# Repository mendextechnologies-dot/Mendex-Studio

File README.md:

# Mendex Engineering Studio v0.1.0 — foundation

**Product documents:** start at `C:\Mendex studio\Product Documents` or the
**Mendex Products** desktop shortcut. Choose the product code, put new incoming
files in `00_Inbox`, and browse managed files under `02_Revision_Files`.
`docs/` is application documentation. Reference and previous project material is
consolidated under `C:\Mendex studio\Engineering References`; no separate Power
Electronics workspace is needed.
Refresh product/revision navigation with `scripts\sync_product_document_hub.ps1`.

**Codex v1.5 workstream:** this review branch extends the released foundation with an 18-entry Tool Center, generic synthetic job queue, logs/evidence previews, reports and dataset-provenance UI. Frozen Agent 1/Agent 2 interface: `12b56c3` / `contracts/v1.5.0`. See [implementation status](docs/IMPLEMENTATION_STATUS.md), [integration usage](docs/INTEGRATIONS.md) and [Agent 2 handoff](docs/AGENT2_HANDOFF.md). Native connector code is not merged or automatically trusted, and this branch is not a full-v1.5 release.

Local Python/PySide6 desktop with SQLite products, typed specifications, immutable previous revisions, filesystem workspaces, native-tool discovery, manual evidence records and draft reports. No engineering calculations or simulation results are produced by the application.

## Install and run (PowerShell)

Tested Python runtime: 3.13.7 x64. Runtime diagnostics report Windows 11 build 26300; the initial Windows marketing-name query returned Windows 10 Home. Only this development workstation has been tested; other machines remain unqualified.

Repository: https://github.com/mendextechnologies-dot/Mendex-Studio · working branch: `main`.

Clone and bootstrap (Git, Python 3.13 and VS Code must be separately installed):

```powershell
git clone https://github.com/mendextechnologies-dot/Mendex-Studio.git
cd Mendex-Studio
powershell -NoProfile -ExecutionPolicy Bypass -File scripts/bootstrap.ps1
.venv\Scripts\python -m mendex_ui
```

The bootstrap sets up only this repository's virtual environment, runs local tests and Doctor, and never installs native engineering tools. `ExecutionPolicy Bypass` applies only to that PowerShell invocation; it does not change system policy.

Equivalent manual setup:

```powershell
python -m venv .venv
.venv\Scripts\python -m pip install -r requirements-lock.txt
.venv\Scripts\python -m pip install -e . --no-deps
.venv\Scripts\python -m pytest -q
.venv\Scripts\python -m mendex_ui
```

Use `--root C:\YourDataFolder` to select a different data directory. Both UI and CLI default to the current directory. Never delete `.mendex` to upgrade; back up `.mendex` and `products` together with the application closed.

```powershell
.venv\Scripts\python -m mendex_core.cli create MC-100 "Transformer pilot" --owner "Engineer"
.venv\Scripts\python -m mendex_core.cli products
.venv\Scripts\python -m mendex_core.cli tools
```

Create products in Products, edit the typed JSON specification, save, then create R002 to preserve R001. Null fields mean unspecified; SI field names carry units. Revision snapshots copy specifications only; native CAD files are not automatically copied. Archived specifications cannot be edited.

## Engineering workflow

1. Select a product and revision in Products. Engineering module screens show its native-file folders and required inputs.
2. Open Tool Manager. Use discovery or browse to an installed executable and Save path. FOUND_UNVERIFIED means compatibility and benchmarks are pending, not ready to simulate. Unknown versions remain unknown. No native tool is launched.
3. Open Validation and record a manual check. The default NOT_EVALUATED entry needs a check ID, reviewer and notes. To record PASS/FAIL, attach an actual evidence file (up to 50 MiB), supply a value and SI unit, and enter minimum and/or maximum. The requested status must match that inclusive numerical criterion. All values, evidence classifications and reviewer identities are manually supplied.
4. Open Reports, Generate draft dossier, select it and Open selected report. The HTML and `snapshot.json` contain frozen specifications, validation history, hashes, tool inventory and warnings. No released status is available.
5. In Products, use Open in VS Code to open the selected revision folder, Open workspace for File Explorer, or Open project file for an associated native application. Files must be inside that revision workspace and use a supported document/CAD extension. Scripts and executables cannot be opened through this action. VS Code, Windows associations and CAD applications must already be installed.
6. In Tool Manager, Run workstation doctor or Export diagnostics. Exports stay under `.mendex/diagnostics`; review environment paths before sharing.
7. In Knowledge Center, review category-specific Engineering rules, loaded/rejected Plugins and the AI interface's explicit availability response. No provider or network connection is configured; no AI-generated engineering answer is produced.
8. In Simulations, record an availability request. It persists the input snapshot and tool metadata as NOT_SUPPORTED, with no solver start or result. This is a job-model foundation, not a simulation runner.

Draft revisions can be renamed or placed In Review. Review locks specification edits until returned to Draft; archived baselines cannot be reopened. Neither state grants product approval. Export specification creates a new JSON snapshot under requirements/; the database remains canonical. Product and specification edits save atomically. Evidence files keep their original name in metadata and use compact internal paths; Open selected evidence checks the hash before invoking an allowed document association.

Evidence copies and metadata are append-only through the service. If specifications change, existing check records remain historical and their effective status becomes NOT_EVALUATED. Missing/modified evidence also becomes NOT_EVALUATED on recheck. Creating a new revision starts a new validation history. Reports do not infer an overall approval from historical PASS entries.

```powershell
.venv\Scripts\python -m mendex_core.cli validation --revision <revision-uuid>
.venv\Scripts\python -m mendex_core.cli report --revision <revision-uuid>
.venv\Scripts\python -m mendex_core.cli open-vscode --revision <revision-uuid>
.venv\Scripts\python -m mendex_core.cli open-file --revision <revision-uuid> requirements/spec.json
.venv\Scripts\python -m mendex_core.doctor --export
.venv\Scripts\python -m mendex_core.cli rules
.venv\Scripts\python -m mendex_core.cli plugins
.venv\Scripts\python -m mendex_core.cli request-simulation --revision <revision-uuid> --tool ltspice
.venv\Scripts\python -m mendex_core.cli runs --revision <revision-uuid>
.venv\Scripts\python scripts/desktop_smoke.py
```

Doctor returns exit code 0 when the Python/Qt/SQLite framework is usable. Its workstation status remains PARTIAL while native tools and benchmarks are unqualified. BLOCKED or invalid CLI operations return a nonzero exit code with actionable JSON diagnostics. A successful process handoff does not prove a CAD application opened or executed correctly.

To verify a non-editable wheel installation in a fresh environment on this workstation:

```powershell
powershell -NoProfile -ExecutionPolicy Bypass -File scripts/verify_install.ps1
```

This retains the verification environment in ignored `.mendex/qa`; it does not replace a second-engineer clean-machine acceptance test. See [manual acceptance](docs/manual-acceptance.md) for the remaining release gates.

Database schema v3 migrates existing v1/v2 data automatically and preserves evidence. Before upgrading, close Studio and back up `.mendex` and `products` together. To roll back the application, restore the matching pre-upgrade backup; do not open v3 data with an older build. HTML/JSON are the supported draft formats; Word/PDF export remains a post-foundation enhancement.

Data-only plugins can extend discovery and rules using [the template](templates/plugins/example-discovery.json); see [configuration instructions](config/README.md). The loader rejects invalid/conflicting manifests without importing Python. Built-in metadata and rule resources ship inside the wheel. Tool versions are read from available Windows file metadata; runtime compatibility remains unqualified.

Manual primary-workstation handoff and packaging commands:

```powershell
.venv\Scripts\python scripts/interactive_acceptance.py --launch
powershell -NoProfile -ExecutionPolicy Bypass -File scripts/package.ps1
```

The first command opens actual VS Code, File Explorer and a harmless uniquely named text fixture, observes the matching windows and retains an acceptance record under ignored `.mendex/qa`. The second requires committed sources, runs local tests and produces a wheel/source archive/checksums under `dist`. Neither command runs a simulator, controls hardware or deploys software. The [v0.1 requirements matrix](docs/requirements-matrix.md) records what is implemented and what the final addendum explicitly excludes.

See [implementation checklist](docs/implementation-checklist.md), [architecture](docs/architecture.md) and [known limitations](docs/known-limitations.md). No CI/CD or deployments are configured.

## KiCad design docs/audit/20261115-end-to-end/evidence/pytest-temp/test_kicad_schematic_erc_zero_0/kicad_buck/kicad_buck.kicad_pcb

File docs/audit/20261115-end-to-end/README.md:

# Mendex Engineering Studio — end-to-end capability and handover audit

**15 November 2026 · AUDIT-1 · Leadership review copy**

**Conclusion: useful engineering framework with working native tool paths; complete manufacturing and production readiness is not demonstrated.** Current release, thermal, tolerance, sourcing and laboratory-document paths contain evidence or completeness weaknesses. No particular product is being approved or developed.

## Reports

1. [Engineering Studio Capability Matrix](01_CAPABILITY_MATRIX.md)
2. [End-to-End Engineering Workflow](02_ENGINEERING_WORKFLOW.md)
3. [Engineering Specifications Report](03_ENGINEERING_SPECIFICATIONS.md)
4. [Manufacturing File Inventory](04_MANUFACTURING_FILE_INVENTORY.md) and [machine-readable inventory](manufacturing-file-inventory.csv)
5. [Team-Wise Handover Guide](05_TEAM_HANDOVER_GUIDE.md)
6. [Manufacturing Readiness Assessment](06_MANUFACTURING_READINESS.md)
7. [Gap Analysis and Implementation Roadmap](07_GAP_ANALYSIS_ROADMAP.md)
8. [Final Executive Summary](08_EXECUTIVE_SUMMARY.md)

## Method, scope and limits

Read `docs/architecture.md`, `docs/engineering-rules.md`, `contracts/README.md` and repository AGENTS.md first. Inspected current core, desktop RPC, React source, native adapters, Copper, generators, lifecycle, evidence, calculations, test plans, procurement and packager. Used read-only SQLite URI, source/data checksums, file inventories, existing logs and isolated local tests/probes. No installations, application fixes, hardware control, communications to teams, deployments or manufacturing approvals were performed. Documentation and disposable audit outputs are the only intentional changes.

The git identity is recorded in [git-before.json](evidence/git-before.json); source and data hashes in [snapshot-before.json](evidence/snapshot-before.json) and the final preservation comparison. Working-tree files can change while a desktop session is running; any changes are disclosed rather than reverted. The audit does not establish that every existing record or approval is valid. A count of measurements or approval rows is not proof of laboratory activity, authenticated identity, or release authorization.

Audit database operations used `evidence/isolated/`. Pytest used `evidence/pytest-temp/` and ran from this evidence directory, so tests using `Path('.')` cannot reach the project database. The laboratory-plan and pricing tests that explicitly require live EMC-100/SV-1000 products were excluded; equivalent generic probes use disposable records. Existing raw evidence, frozen revisions and earlier audit reports were not repaired or overwritten. Audit placeholders are conspicuously labeled. The sole checklist addition records audit completion, not implementation.

## Evidence register

| ID | Evidence | What it establishes |
| --- | --- | --- |
| E01 | [snapshot-before.json](evidence/snapshot-before.json), [git-before.json](evidence/git-before.json) | Source/data identities; scope of assessed working tree |
| E02 | [tool-discovery.json](evidence/tool-discovery.json), [native-tools.json](evidence/native-tools.json) | Actual resolved paths, reported versions, discovery vs executable behavior |
| E03 | [database-readonly.json](evidence/database-readonly.json) | Schema version, integrity and row counts only |
| E04 | [artifact-inventory.json](evidence/artifact-inventory.json) | Existing file paths, sizes, SHA-256; not design acceptance |
| E05 | [probe-results.json](evidence/probe-results.json), [audit_probe.py](evidence/audit_probe.py) | Repeatable isolated negative and packaging probes |
| E06 | [pytest.log](evidence/pytest.log), [pytest.xml](evidence/pytest.xml), [verification summary](evidence/verification-summary.md) | Selected local regression results; per-test interpretation |
| E07 | [typescript.log](evidence/typescript.log) | TypeScript no-emit check; no application bundle was rebuilt |
| E08 | [preservation.json](evidence/preservation.json) | Before/after changes to monitored source and live data |
| E09 | [earlier native exercise](../MENDEX_POWER_ELECTRONICS_END_TO_END_READINESS.md) and its evidence | Historical 14-Nov native run, not a fresh acceptance result |

An initial probe encountered the real empty-specification laboratory-plan TypeError. A continuation corrected an audit-harness reference from `Revision.status` to `lifecycle_status`; the latter was a harness mistake, not an application defect. [probe.log](evidence/probe.log) preserves that failure. No production fix was applied.

## Status interpretation

Use the six requested implementation classes: Fully implemented and verified; Implemented but not tested; Partially implemented; Integration available but not operational; Not implemented; Blocked by external dependency. They describe software scope. Separately mark engineering acceptance as evaluated or NOT_EVALUATED. “READY” from discovery or ZIP availability must never be silently promoted to fabrication, safety or production readiness.

## Assessment cutoff

15 November 2026, 14:40:18 Asia/Calcutta. [Closing addendum](09_CLOSING_SOURCE_ADDENDUM.md) records concurrent mechanical packaging/route additions. Final isolated probe confirms STEP is now collected, simulations/requirements are still omitted, and incomplete/corrupt ZIPs still report READY. Later edits are outside this audit.

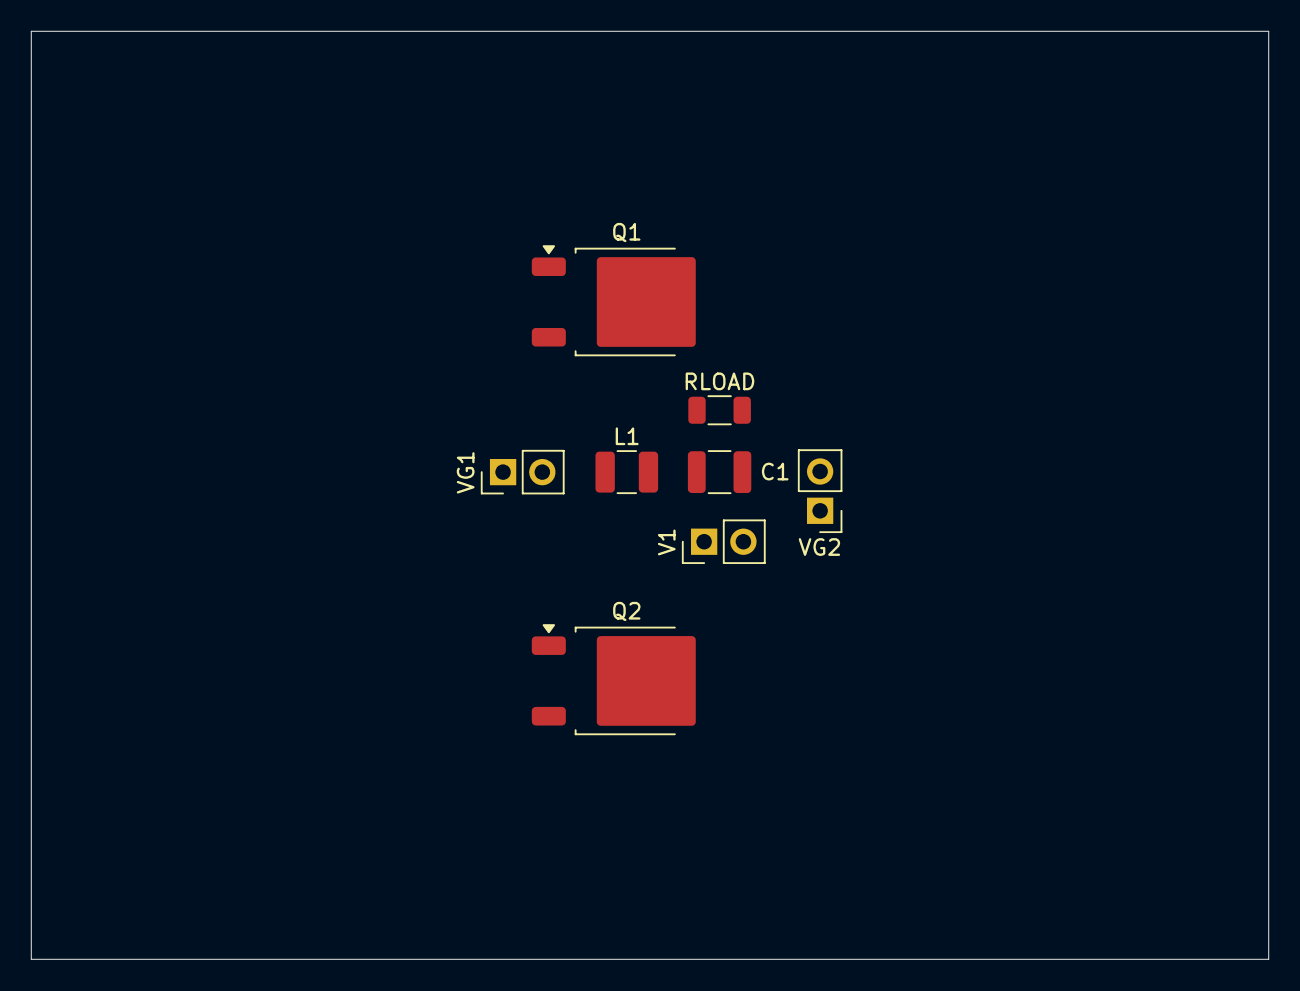
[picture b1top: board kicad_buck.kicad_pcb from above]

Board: 2 copper layers, 80.0 x 60.0 mm, 8 parts (0 on the bottom side), 3 nets, no tracks yet.

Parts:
C1: 4.7e-05 F; C_1210_3225Metric
L1: 4.7e-05 H; L_1210_3225Metric
Q1: High-Side Power MOSFET; TO-252-2
Q2: Synchronous Low-Side Power MOSFET; TO-252-2
RLOAD: 5 Ohm; R_1206_3216Metric
V1: 12 V; PinHeader_1x02_P2.54mm_Vertical
VG1, VG2: 10 V; PinHeader_1x02_P2.54mm_Vertical

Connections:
/SW: L1.1, VG1.2
/VOUT: C1.1, L1.2, RLOAD.1
GND: C1.2, RLOAD.2, V1.2, VG2.2

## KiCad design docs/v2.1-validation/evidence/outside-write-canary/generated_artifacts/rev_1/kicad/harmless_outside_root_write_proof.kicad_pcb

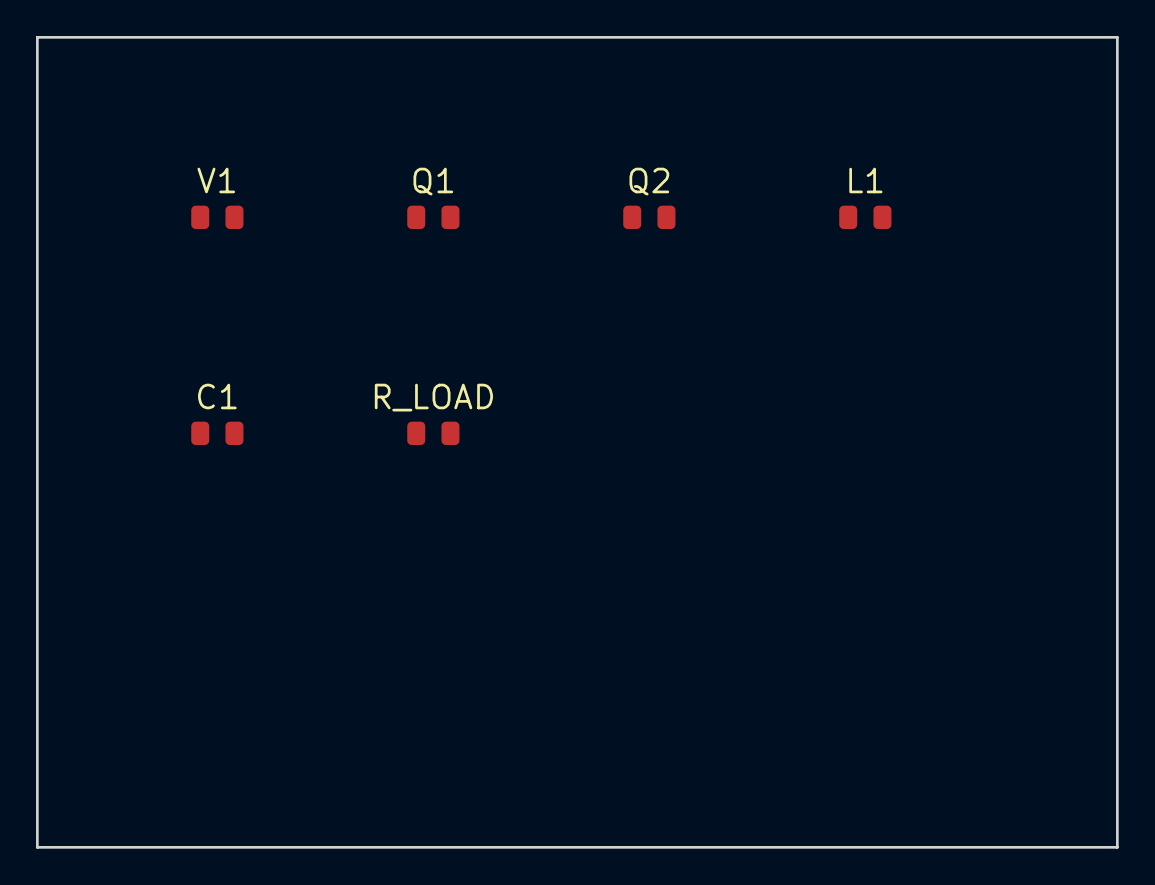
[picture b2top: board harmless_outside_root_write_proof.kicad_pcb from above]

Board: 2 copper layers, 60.0 x 45.0 mm, 6 parts (0 on the bottom side), 2 nets, no tracks yet.

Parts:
C1: Output Filter Capacitor; R_0805_2012Metric
L1: Power Inductor; R_0805_2012Metric
Q1: High-Side Switch; R_0805_2012Metric
Q2: Synchronous Low-Side Switch; R_0805_2012Metric
R_LOAD: Load Resistor; R_0805_2012Metric
V1: Input DC Supply; R_0805_2012Metric

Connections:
SW: C1.2, L1.2, Q1.2, Q2.2, R_LOAD.2, V1.2
VIN: C1.1, L1.1, Q1.1, Q2.1, R_LOAD.1, V1.1

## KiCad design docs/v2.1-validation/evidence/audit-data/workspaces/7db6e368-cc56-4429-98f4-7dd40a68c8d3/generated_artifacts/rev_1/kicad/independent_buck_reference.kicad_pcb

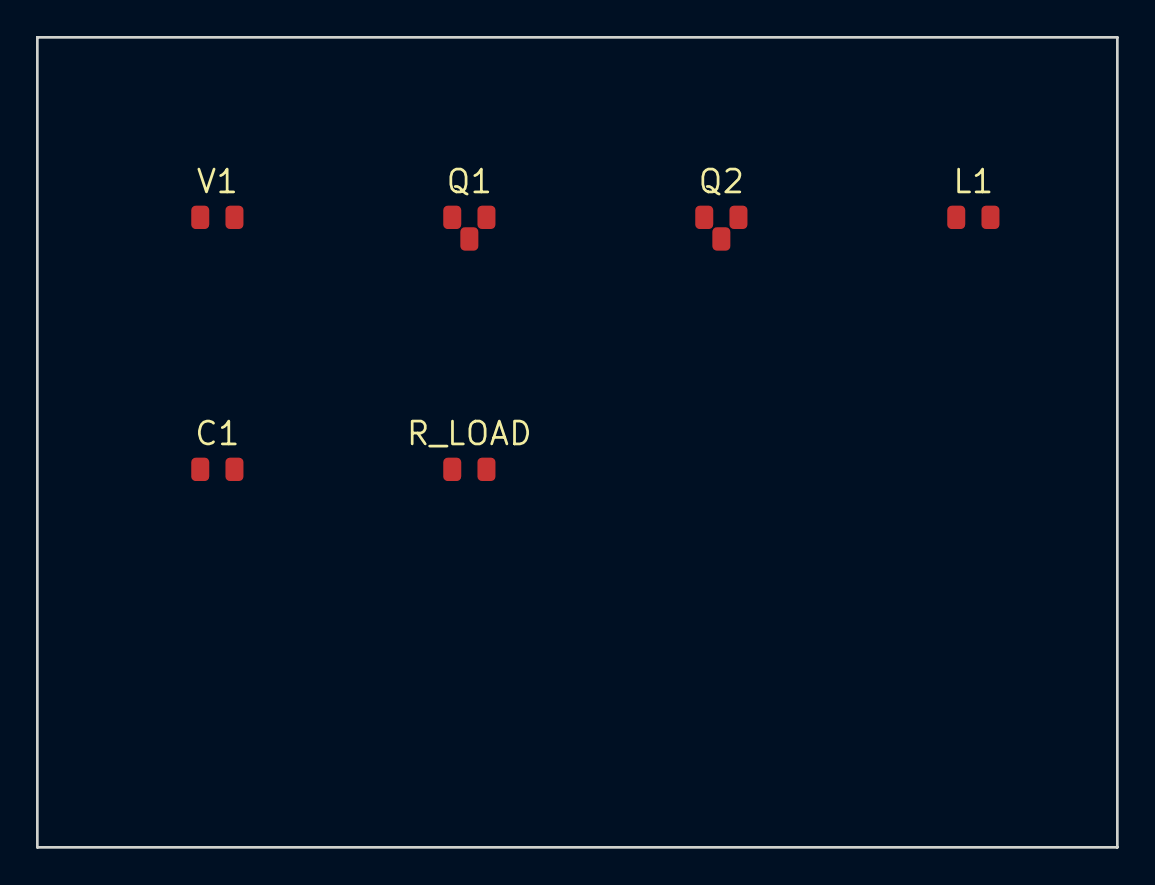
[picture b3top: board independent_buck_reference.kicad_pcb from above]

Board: 2 copper layers, 60.0 x 45.0 mm, 6 parts (0 on the bottom side), 4 nets, no tracks yet.

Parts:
C1: Output Filter Capacitor; R_0805_2012Metric
L1: Power Inductor; R_0805_2012Metric
Q1: High-Side Switch; R_0805_2012Metric
Q2: Synchronous Low-Side Switch; R_0805_2012Metric
R_LOAD: Load Resistor; R_0805_2012Metric
V1: Input DC Supply; R_0805_2012Metric

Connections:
GND: C1.2, Q2.s, R_LOAD.2, V1.n
SW: L1.1, Q1.s, Q2.d
VIN: Q1.d, V1.p
VOUT: C1.1, L1.2, R_LOAD.1

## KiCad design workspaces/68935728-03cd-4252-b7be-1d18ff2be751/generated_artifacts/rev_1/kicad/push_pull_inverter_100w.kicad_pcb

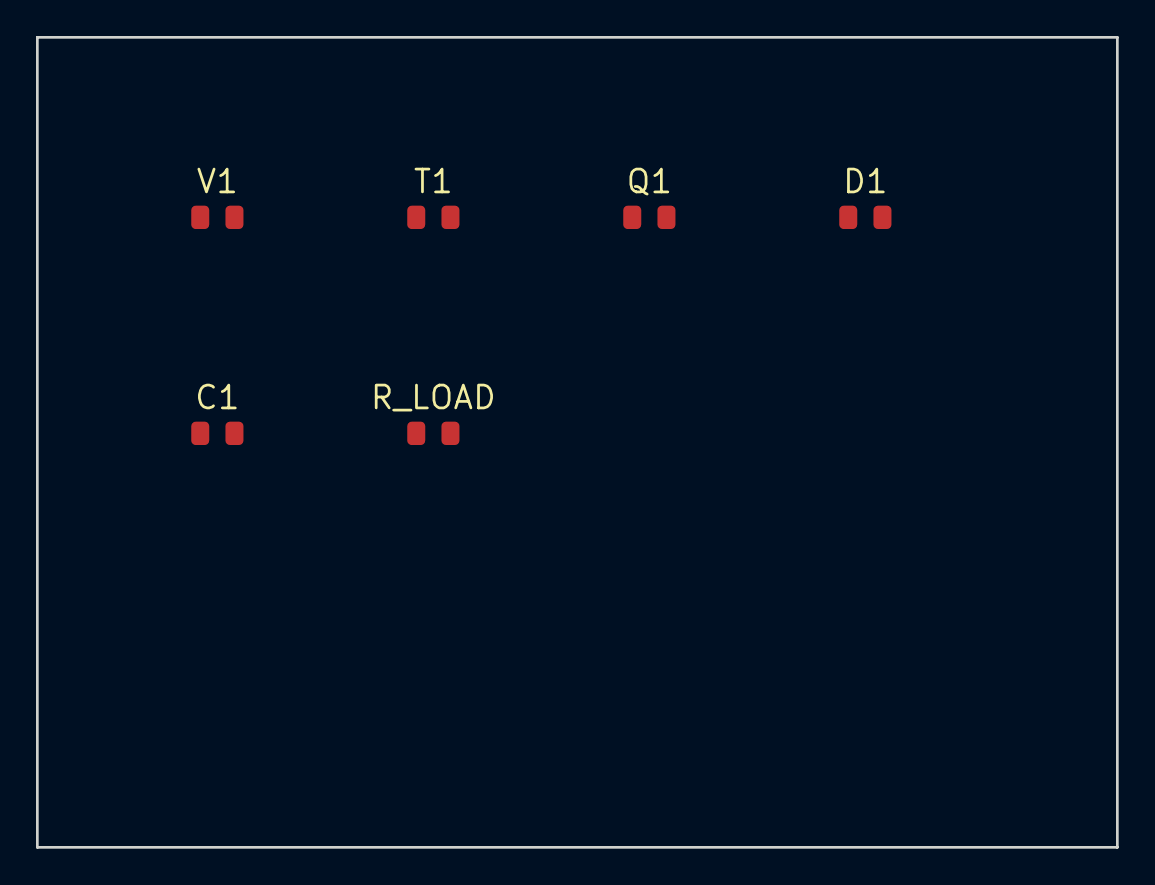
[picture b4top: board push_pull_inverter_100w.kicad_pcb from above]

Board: 2 copper layers, 60.0 x 45.0 mm, 6 parts (0 on the bottom side), 2 nets, no tracks yet.

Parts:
C1: Secondary Output Capacitor; R_0805_2012Metric
D1: Secondary Rectifier Diode; R_0805_2012Metric
Q1: Primary Switching MOSFET; R_0805_2012Metric
R_LOAD: Output Load; R_0805_2012Metric
T1: Coupled Flyback Transformer; R_0805_2012Metric
V1: Input DC Supply; R_0805_2012Metric

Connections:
DRAIN: C1.2, D1.2, Q1.2, R_LOAD.2, T1.2, V1.2
VIN: C1.1, D1.1, Q1.1, R_LOAD.1, T1.1, V1.1
